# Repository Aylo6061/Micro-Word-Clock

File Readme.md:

# Micro Word Clock Kicad Edition!

## Description
Updated version of the micro word clock, laid out in Kicad for your viewing/editing pleasure.  This uses the commonly avalible adafruit matrix and has a battery backup for the RTC and a USB power jack.  This way it can be programmed once and whenever it is plugged in it should have the right time.

Per original description:

A tiny replica of the famous Word Clock, using only an ATmega microcontroller, a DS1307 Real Time Clock and a few passive components to display the time on an 8x8 LED matrix. The letters have been printed onto a transparent sheet and glued over the LEDs to produce a readable time.
See the YouTube video [here](https://www.youtube.com/watch?v=9ko9CeylUTs).

## Directory structure
- **MicroWordClock2-Arduino** contains the firmware, including pin definitions for the LED matrix and location of the words in each language.
- **KiCad** contains the schematic and PCB design files for the proeject.
- **Graphics** contains the design for the transparency sheet to place over the LED matrix to form the words, designed in Inkscape. Contributions in more languages are welcome!

## Bill of Materials

|            | Part name          | Package size                 | [Digikey](www.digikey.com) part number                                                                                        |
|------------|--------------------|------------------------------|--------------------------------------------------------------------------------------------------------------------------------|
| U1        | ATmega328P-AU      | TQFP-32                      | ATMEGA328P-AURCT-ND                                                                                                                 |
| U3        | DS1307Z+           | SO-8                         | DS1307Z+-ND                                                                                                                      |
| C1         | 1uF cap      | 2012 metric / 0805 imperial  | 1276-6471-1-ND                                                                                                                |
| C2         | 1uF cap      | 2012 metric / 0805 imperial  | 1276-6471-1-ND                                                                                                                |
| SW1         | SMD push button    | "nanoT" aka VERY small                   | 108-NANOT240BSCT-ND                                                  |
| Y1       | 32.768 kHz crystal | 3216 metric / 1206 imperial  | 1908-1314-1-ND                                                                                                              |
| LED matrix | 8x8 matrix         | 20x20mm                      | [8x8 adafruit](https://www.adafruit.com/product/454https://www.adafruit.com/product/454)  |
| J1         | USB connector      | smd connector | 609-4613-1-ND|
|BT1 | 3v lithium battery | thru hole tabs|	P192-ND | 
| PCB        |                    | 20x20mm                      | [Order from osh park](https://oshpark.com/shared_projects/m8JDYR6z)                                                                     
## NB!!! Here be dragons!!! Warnings etc.

You will require an In-System Programmer (ISP) to write the firmware onto the microcontroller.

You will also need some way of attaching the ISP- I did not put nice pads on here for a standard atmel ISP header, instead these traces are routed to a board edge connector that I connected to with pogo pins. A standard .1" header stick could be soldered on for programming, or you could probably just push hard and get it to connect for a few seconds while you program.

The battery is not neccesary for this project to work- however if you do not have it, the clock will forget what time it is every time it is unplugged.

The button is VERY small.  If you dont like really trick surface mount soldering, you can omit it, but you wont be able to set the time.  If you have the battery mounted, this won't matter as the clock will remember what time it is (or if you experience DST or time zones changes).

## Burning the bootloader and uploading the sketch
Please download Carlos Rodrigues' Barebones ATmega Chips board configuration file:
https://github.com/carlosefr/atmega (instructions inside)

The ICSP header on the Micro Word Clock PCB is the silkscreened on the board.

## Contributions
Carl Monk has built [his own version](http://fortoffee.org.uk/2014/12/word-clock-with-a-unicorn/) using a [Unicorn HAT](http://shop.pimoroni.com/products/unicorn-hat).

[quistoph](https://github.com/qistoph) has made a Dutch layout.

Tanguy Rewers independently came up with an alternative Dutch layout (labeled as dutch2).

## License
This project (both software and hardware) is published under a [Creative Commons BY-SA 3.0 License](http://creativecommons.org/licenses/by-sa/3.0/).

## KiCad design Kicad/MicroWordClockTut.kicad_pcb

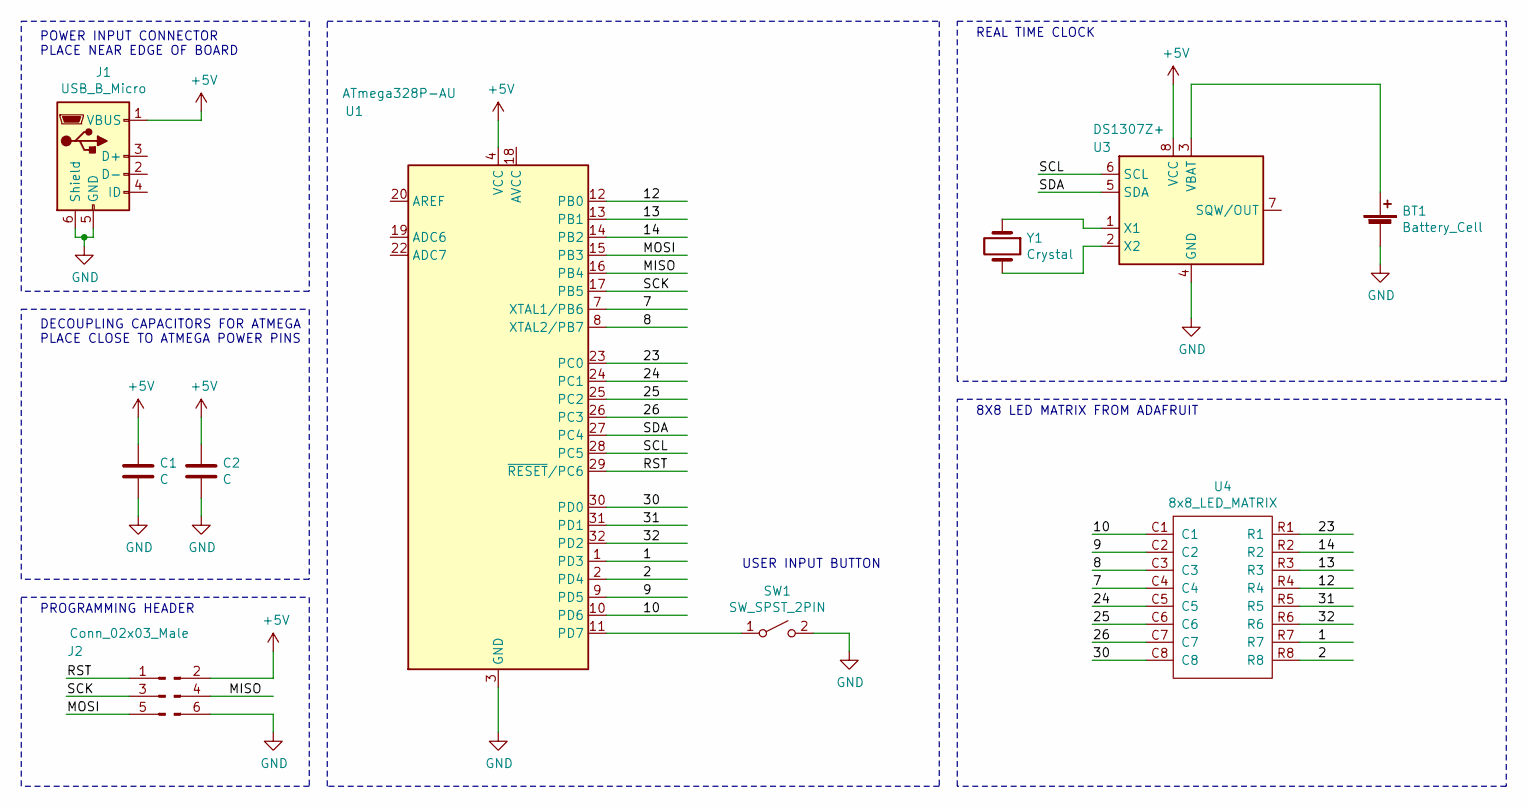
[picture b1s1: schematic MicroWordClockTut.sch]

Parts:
BT1: Battery_Cell; BR1225VCN
C1, C2: C; C_0805_HandSoldering
J1: USB_B_Micro; 10118192-0001LF
J2: Conn_02x03_Male; side connector
SW1: SW_SPST_2PIN; NanoT BS
U1: ATmega328P-AU; TQFP-32_7x7mm_Pitch0.8mm
U3: DS1307Z+; SOIC-8_3.9x4.9mm_Pitch1.27mm
U4: 8x8_LED_MATRIX; KWM-20882XVB
Y1: Crystal; 2-SMD XTAL CC7-T1A

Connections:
+5V: C1.1, C2.1, J1.1 (VBUS), J2.2, U1.4 (VCC), U1.6 (VCC), U3.8 (VCC)
/1: U1.1 (PD3), U4.R7
/2: U1.2 (PD4), U4.R8
/7: U1.7 (XTAL1/PB6), U4.C4
/8: U1.8 (XTAL2/PB7), U4.C3
/9: U1.9 (PD5), U4.C2
/10: U1.10 (PD6), U4.C1
/12: U1.12 (PB0), U4.R4
/13: U1.13 (PB1), U4.R3
/14: U1.14 (PB2), U4.R2
/23: U1.23 (PC0), U4.R1
/24: U1.24 (PC1), U4.C5
/25: U1.25 (PC2), U4.C6
/26: U1.26 (PC3), U4.C7
/30: U1.30 (PD0), U4.C8
/31: U1.31 (PD1), U4.R5
/32: U1.32 (PD2), U4.R6
/MISO: J2.4, U1.16 (PB4)
/MOSI: J2.5, U1.15 (PB3)
/RST: J2.1, U1.29 (~RESET~/PC6)
/SCK: J2.3, U1.17 (PB5)
/SCL: U1.28 (PC5), U3.6 (SCL)
/SDA: U1.27 (PC4), U3.5 (SDA)
GND: BT1.2 (-), C1.2, C2.2, J1.5 (GND), J1.6 (Shield), J2.6, SW1.2 (B), U1.3 (GND), U1.5 (GND), U1.21 (GND), U3.4 (GND)
unnamed: BT1.1 (+), U3.3 (VBAT)
unnamed: SW1.1 (A), U1.11 (PD7)
unnamed: U3.1 (X1), Y1.1
unnamed: U3.2 (X2), Y1.2

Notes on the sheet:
DECOUPLING CAPACITORS FOR ATMEGA PLACE CLOSE TO ATMEGA POWER PINS
POWER INPUT CONNECTOR PLACE NEAR EDGE OF BOARD
PROGRAMMING HEADER
USER INPUT BUTTON
REAL TIME CLOCK
8X8 LED MATRIX FROM ADAFRUIT

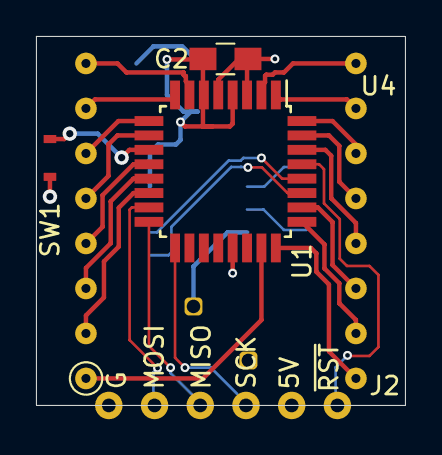
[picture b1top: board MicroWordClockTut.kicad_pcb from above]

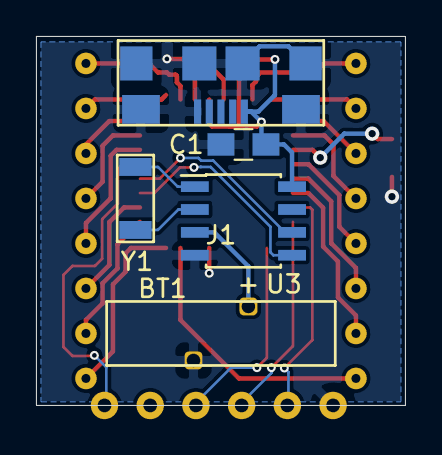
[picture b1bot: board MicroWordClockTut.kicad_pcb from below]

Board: 2 copper layers, 20.5 x 20.5 mm, 10 parts (5 on the bottom side), 28 nets.

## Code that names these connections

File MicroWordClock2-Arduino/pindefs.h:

// Matching LED rows/columns to the matrix's pins
// to microcontroller ports to microcontroller pins
// to Arduino pin notation. Whew.

// PORTB: Digital pins (offset 8), PB6/PB7 are XTAL
// PORTC: Analog pins (no offset), PC6 is RESET, PC7 nonexistent
// PORTD: Digital pins (no offset)

// Pin definitions
#define PIN_BUTTON PD7

// Mapping Matrix Row/Col numbers to Matrix pins
#define MTX_ROW1 MTX_PIN4
#define MTX_ROW2 MTX_PIN3
#define MTX_ROW3 MTX_PIN2
#define MTX_ROW4 MTX_PIN1
#define MTX_ROW5 MTX_PIN9
#define MTX_ROW6 MTX_PIN10
#define MTX_ROW7 MTX_PIN11
#define MTX_ROW8 MTX_PIN12

#define MTX_COL1 MTX_PIN16
#define MTX_COL2 MTX_PIN15
#define MTX_COL3 MTX_PIN14
#define MTX_COL4 MTX_PIN13
#define MTX_COL5 MTX_PIN5
#define MTX_COL6 MTX_PIN6
#define MTX_COL7 MTX_PIN7
#define MTX_COL8 MTX_PIN8

#define MTX_PIN1  SIG_23
#define MTX_PIN2  SIG_14
#define MTX_PIN3  SIG_13
#define MTX_PIN4  SIG_12
#define MTX_PIN5  SIG_10
#define MTX_PIN6  SIG_9
#define MTX_PIN7  SIG_8
#define MTX_PIN8  SIG_7
#define MTX_PIN9  SIG_2
#define MTX_PIN10 SIG_1
#define MTX_PIN11 SIG_32
#define MTX_PIN12 SIG_31
#define MTX_PIN13 SIG_30
#define MTX_PIN14 SIG_26
#define MTX_PIN15 SIG_25
#define MTX_PIN16 SIG_24

#define SIG_24  PC1
#define SIG_23  PC0
#define SIG_14  PB2
#define SIG_13  PB1
#define SIG_9   PD5
#define SIG_12  PB0
#define SIG_10  PD6
#define SIG_8   PB7
#define SIG_25  PC2
#define SIG_26  PC3
#define SIG_30  PD0
#define SIG_31  PD1
#define SIG_32  PD2
#define SIG_1   PD3
#define SIG_2   PD4
#define SIG_7   PB6

#define PB0  8
#define PB1  9
#define PB2 10
#define PB3 11
#define PB4 12
#define PB5 13
#define PB6 A6 //XTAL1
#define PB7 A7 //XTAL2

#define PC0 A0
#define PC1 A1
#define PC2 A2
#define PC3 A3
#define PC4 A4
#define PC5 A5


#define PD0 0
#define PD1 1
#define PD2 2
#define PD3 3
#define PD4 4
#define PD5 5
#define PD6 6
#define PD7 7

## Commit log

2021-03-02 kicad version using the original matrix and a matrix from luckylight (bought at adafruit). errors are in this initial commit
2021-03-02 changed pindefs to reflect currently committed schematic
2021-03-03 started routing. it is small. pinswapped a lot
2021-03-06 latest version with tiny switch NanoT
2021-03-13 this version released to osh park
2021-04-03 final version of pindefs for the kicad board
2021-04-03 edited readme
2021-04-03 edited readme to include link to pcb
